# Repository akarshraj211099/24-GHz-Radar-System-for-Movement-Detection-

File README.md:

# 24-GHz-Radar-System-for-Movement-Detection-

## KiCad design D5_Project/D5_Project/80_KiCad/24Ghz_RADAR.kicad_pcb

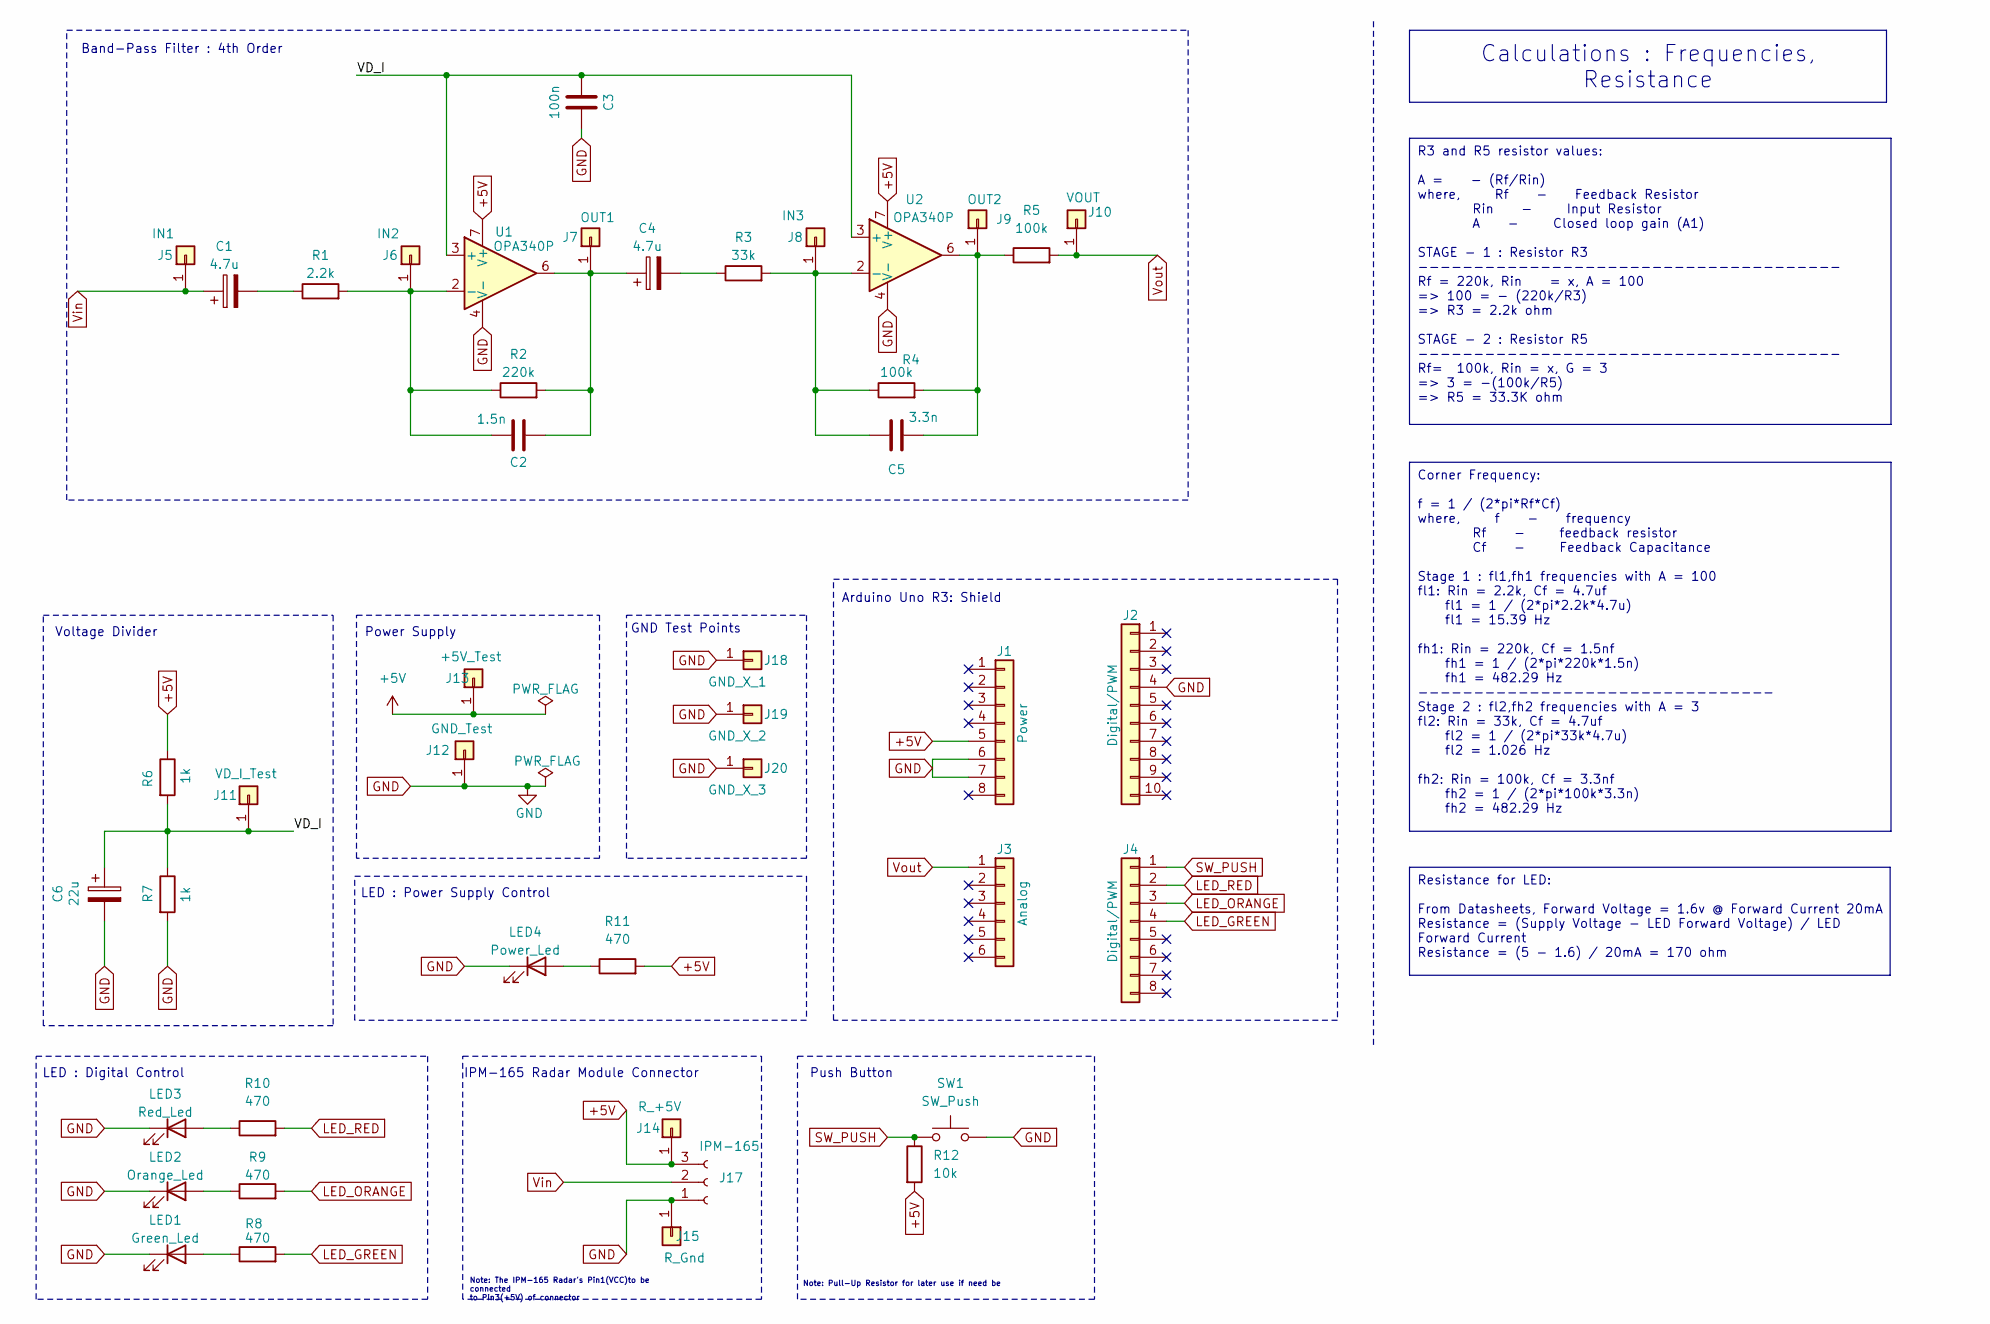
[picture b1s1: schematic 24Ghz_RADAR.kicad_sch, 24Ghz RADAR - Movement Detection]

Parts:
C1, C4: 4.7u; CP_Radial_D5.0mm_P2.50mm
C2: 1.5n; C_Rect_L7.2mm_W7.2mm_P5.00mm_FKS2_FKP2_MKS2_MKP2
C3: 100n; C_Rect_L7.2mm_W2.5mm_P5.00mm_FKS2_FKP2_MKS2_MKP2
C5: 3.3n; C_Rect_L7.2mm_W7.2mm_P5.00mm_FKS2_FKP2_MKS2_MKP2
C6: 22u; CP_Radial_D5.0mm_P2.00mm
J1: Power; PinHeader_1x08_P2.54mm_Vertical
J2: Digital/PWM; PinHeader_1x10_P2.54mm_Vertical
J3: Analog; PinHeader_1x06_P2.54mm_Vertical
J4: Digital/PWM; PinHeader_1x08_P2.54mm_Vertical
J5: IN1; PinHeader_1x01_P2.54mm_Vertical
J6: IN2; PinHeader_1x01_P2.54mm_Vertical
J7: OUT1; PinHeader_1x01_P2.54mm_Vertical
J8: IN3; PinHeader_1x01_P2.54mm_Vertical
J9: OUT2; PinHeader_1x01_P2.54mm_Vertical
J10: VOUT; PinHeader_1x01_P2.54mm_Vertical
J11: VD_I_Test; PinHeader_1x01_P2.54mm_Vertical
J12: GND_Test; PinHeader_1x01_P2.54mm_Vertical
J13: +5V_Test; PinHeader_1x01_P2.54mm_Vertical
J14: R_+5V; PinHeader_1x01_P2.54mm_Vertical
J15: R_Gnd; PinHeader_1x01_P2.54mm_Vertical
J17: IPM-165; PinSocket_1x03_P2.54mm_Horizontal
J18: GND_X_1; PinHeader_1x01_P2.54mm_Vertical
J19: GND_X_2; PinHeader_1x01_P2.54mm_Vertical
J20: GND_X_3; PinHeader_1x01_P2.54mm_Vertical
LED1: Green_Led; LED_D5.0mm
LED2: Orange_Led; LED_D5.0mm
LED3: Red_Led; LED_D5.0mm
LED4: Power_Led; LED_D5.0mm
R1: 2.2k; R_Axial_DIN0207_L6.3mm_D2.5mm_P10.16mm_Horizontal
R2: 220k; R_Axial_DIN0207_L6.3mm_D2.5mm_P10.16mm_Horizontal
R3: 33k; R_Axial_DIN0207_L6.3mm_D2.5mm_P10.16mm_Horizontal
R4, R5: 100k; R_Axial_DIN0207_L6.3mm_D2.5mm_P10.16mm_Horizontal
R6, R7: 1k; R_Axial_DIN0207_L6.3mm_D2.5mm_P10.16mm_Horizontal
R8, R9, R10, R11: 470; R_Axial_DIN0207_L6.3mm_D2.5mm_P10.16mm_Horizontal
R12: 10k; R_Axial_DIN0207_L6.3mm_D2.5mm_P10.16mm_Horizontal
SW1: SW_Push; SW_PUSH_6mm_H7.3mm
U1, U2: OPA340P; DIP-8_W7.62mm

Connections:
+5V: J1.5, J13.1, J14.1, J17.3, R6.1, R11.2, R12.2, U1.7 (V+), U2.7 (V+)
/VD_I: C3.2, C6.1, J11.1, R6.2, R7.1, U1.3 (+), U2.3 (+)
GND: C3.1, C6.2, J1.6, J1.7, J2.4, J12.1, J15.1, J17.1, J18.1, J19.1, J20.1, LED1.1 (K), LED2.1 (K), LED3.1 (K), LED4.1 (K), R7.2, SW1.2, U1.4 (V-), U2.4 (V-)
LED_GREEN: J4.4, R8.2
LED_ORANGE: J4.3, R9.2
LED_RED: J4.2, R10.2
unnamed: C1.2, R1.1
unnamed: C4.2, R3.1
unnamed: C2.1, J6.1, R1.2, R2.1, U1.2 (-)
unnamed: C2.2, C4.1, J7.1, R2.2, U1.6
unnamed: C5.1, J8.1, R3.2, R4.1, U2.2 (-)
unnamed: C5.2, J9.1, R4.2, R5.1, U2.6
unnamed: LED1.2 (A), R8.1
unnamed: LED2.2 (A), R9.1
unnamed: LED3.2 (A), R10.1
unnamed: LED4.2 (A), R11.1
SW_PUSH: J4.1, R12.1, SW1.1
Vin: C1.1, J5.1, J17.2
Vout: J3.1, J10.1, R5.2

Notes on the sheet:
R3 and R5 resistor values: A = - (Rf/Rin) where, Rf - Feedback Resistor Rin - Input Resistor A - Closed loop gain (A1) STAGE - 1 : Resistor R3 -------------------------------------- Rf = 220k, Rin = x, A = 100 => 100 = - (220k/R3) => R3 = 2.2k ohm STAGE - 2 : Resistor R5 ---------------------------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
Corner Frequency: f = 1 / (2*pi*Rf*Cf) where, f - frequency Rf - feedback resistor Cf - Feedback Capacitance Stage 1 : fl1,fh1 frequencies with A = 100 fl1: Rin = 2.2k, Cf = 4.7uf fl1 = 1 / (2*pi*2.2k*4.7u) fl1 = 15.39 Hz fh1: Rin = 220k, Cf = 1.5nf fh1 = 1 / (2*pi*220k*1.5n) fh1 = 482.29 Hz ------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
Calculations : Frequencies, Resistance
Resistance for LED: From Datasheets, Forward Voltage = 1.6v @ Forward Current 20mA Resistance = (Supply Voltage - LED Forward Voltage) / LED Forward Current Resistance = (5 - 1.6) / 20mA = 170 ohm
Note: The IPM-165 Radar's Pin1(VCC)to be connected to Pin3(+5V) of connector
Push Button
GND Test Points
LED : Power Supply Control
IPM-165 Radar Module Connector
Note: Pull-Up Resistor for later use if need be
Power Supply
LED : Digital Control
Band-Pass Filter : 4th Order
Voltage Divider
Arduino Uno R3: Shield

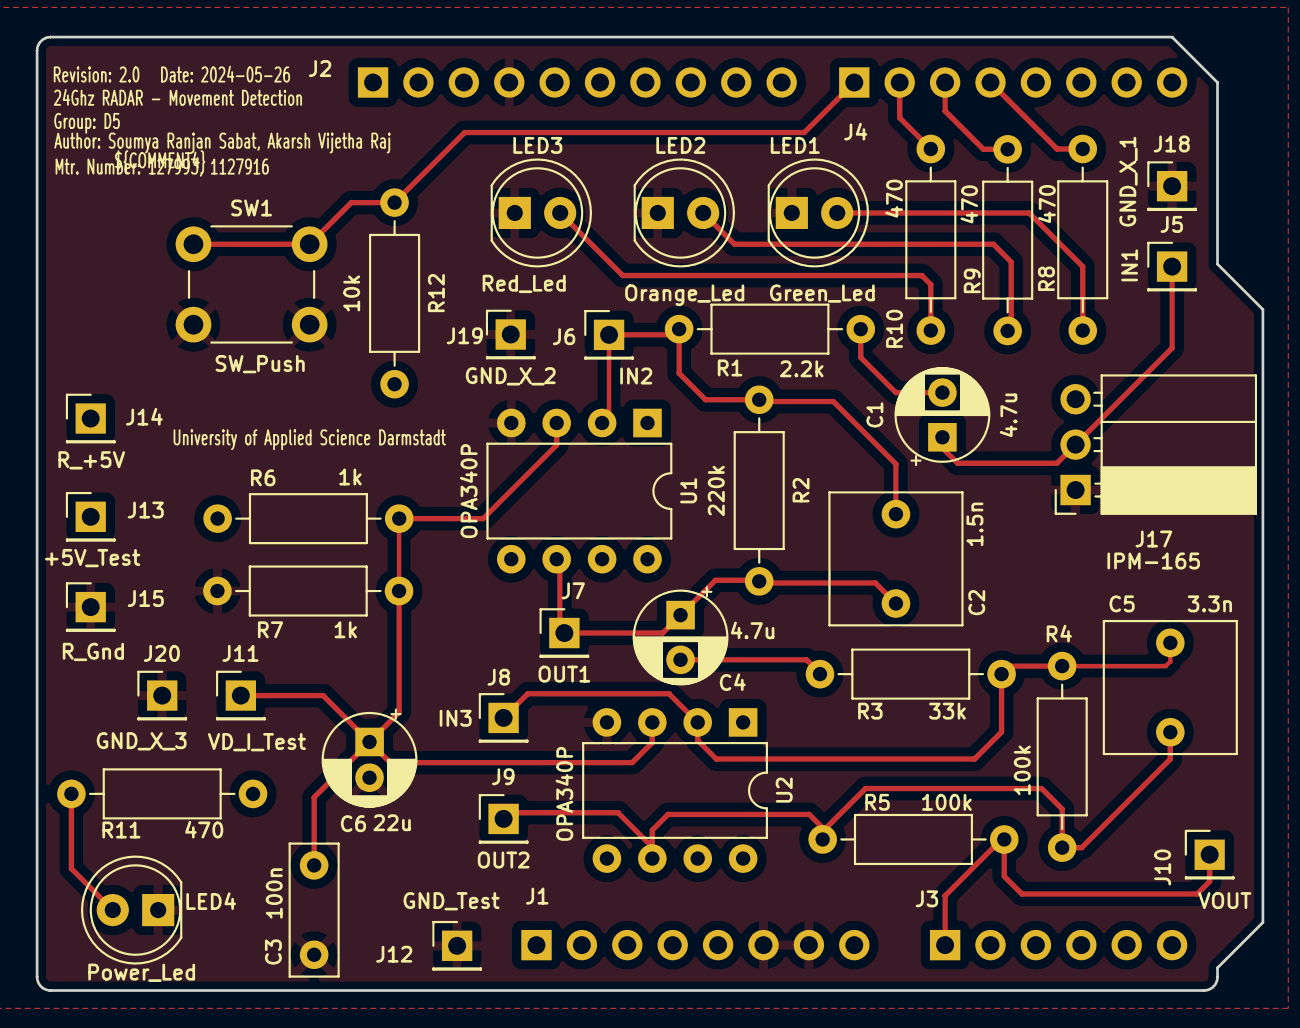
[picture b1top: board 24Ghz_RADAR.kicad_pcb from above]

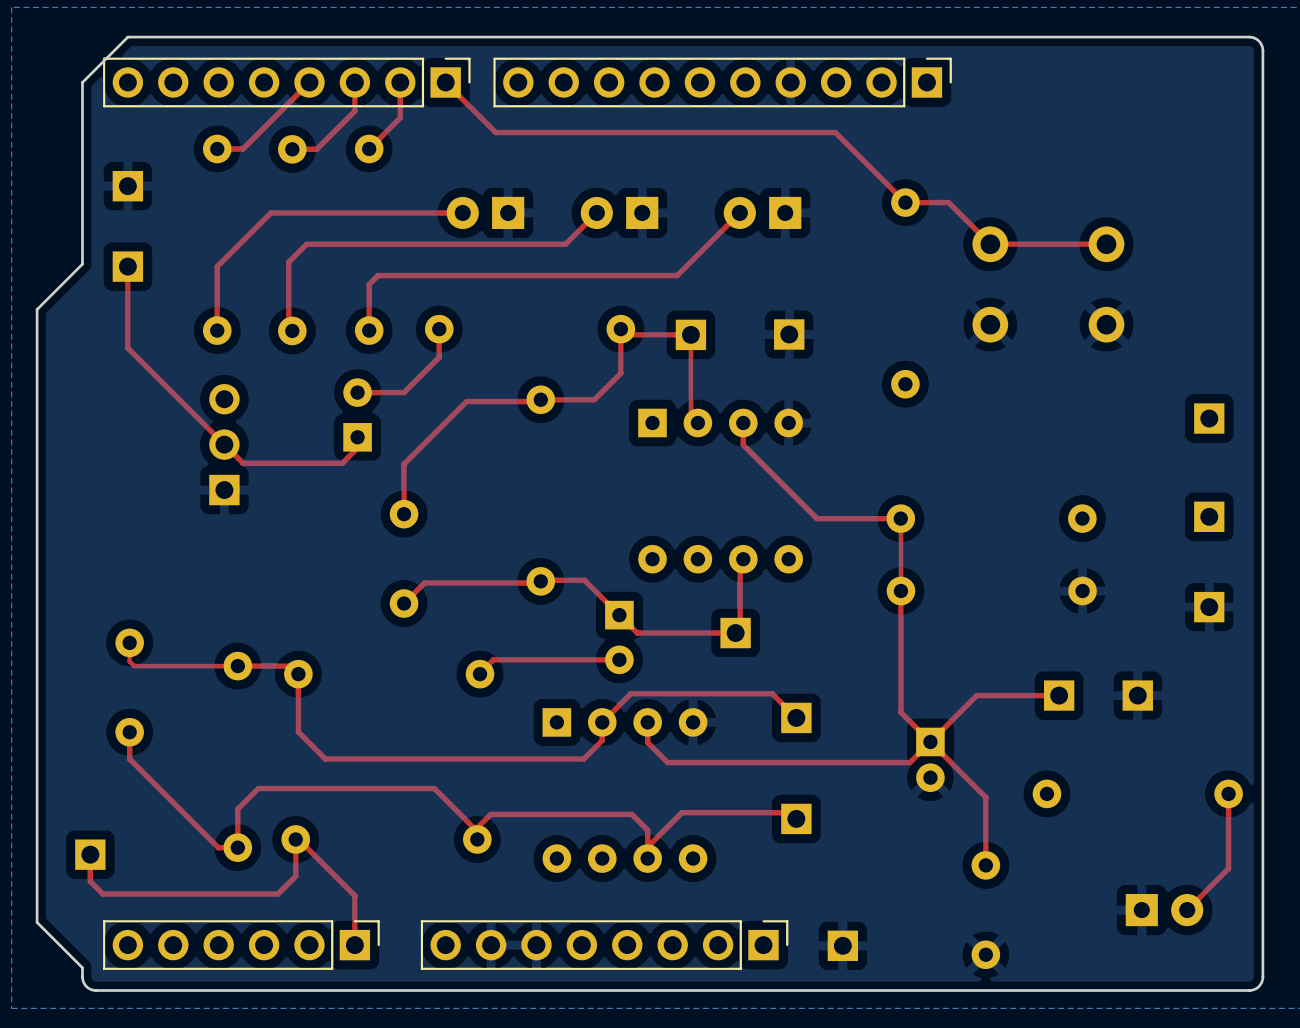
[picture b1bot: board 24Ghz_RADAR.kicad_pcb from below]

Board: 4 copper layers, 68.6 x 53.3 mm, 44 parts (4 on the bottom side), 19 nets.
